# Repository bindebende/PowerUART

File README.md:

# PowerUART
Under Development!!!
USB to UART converter with Type C connector and 100W Power Delivery

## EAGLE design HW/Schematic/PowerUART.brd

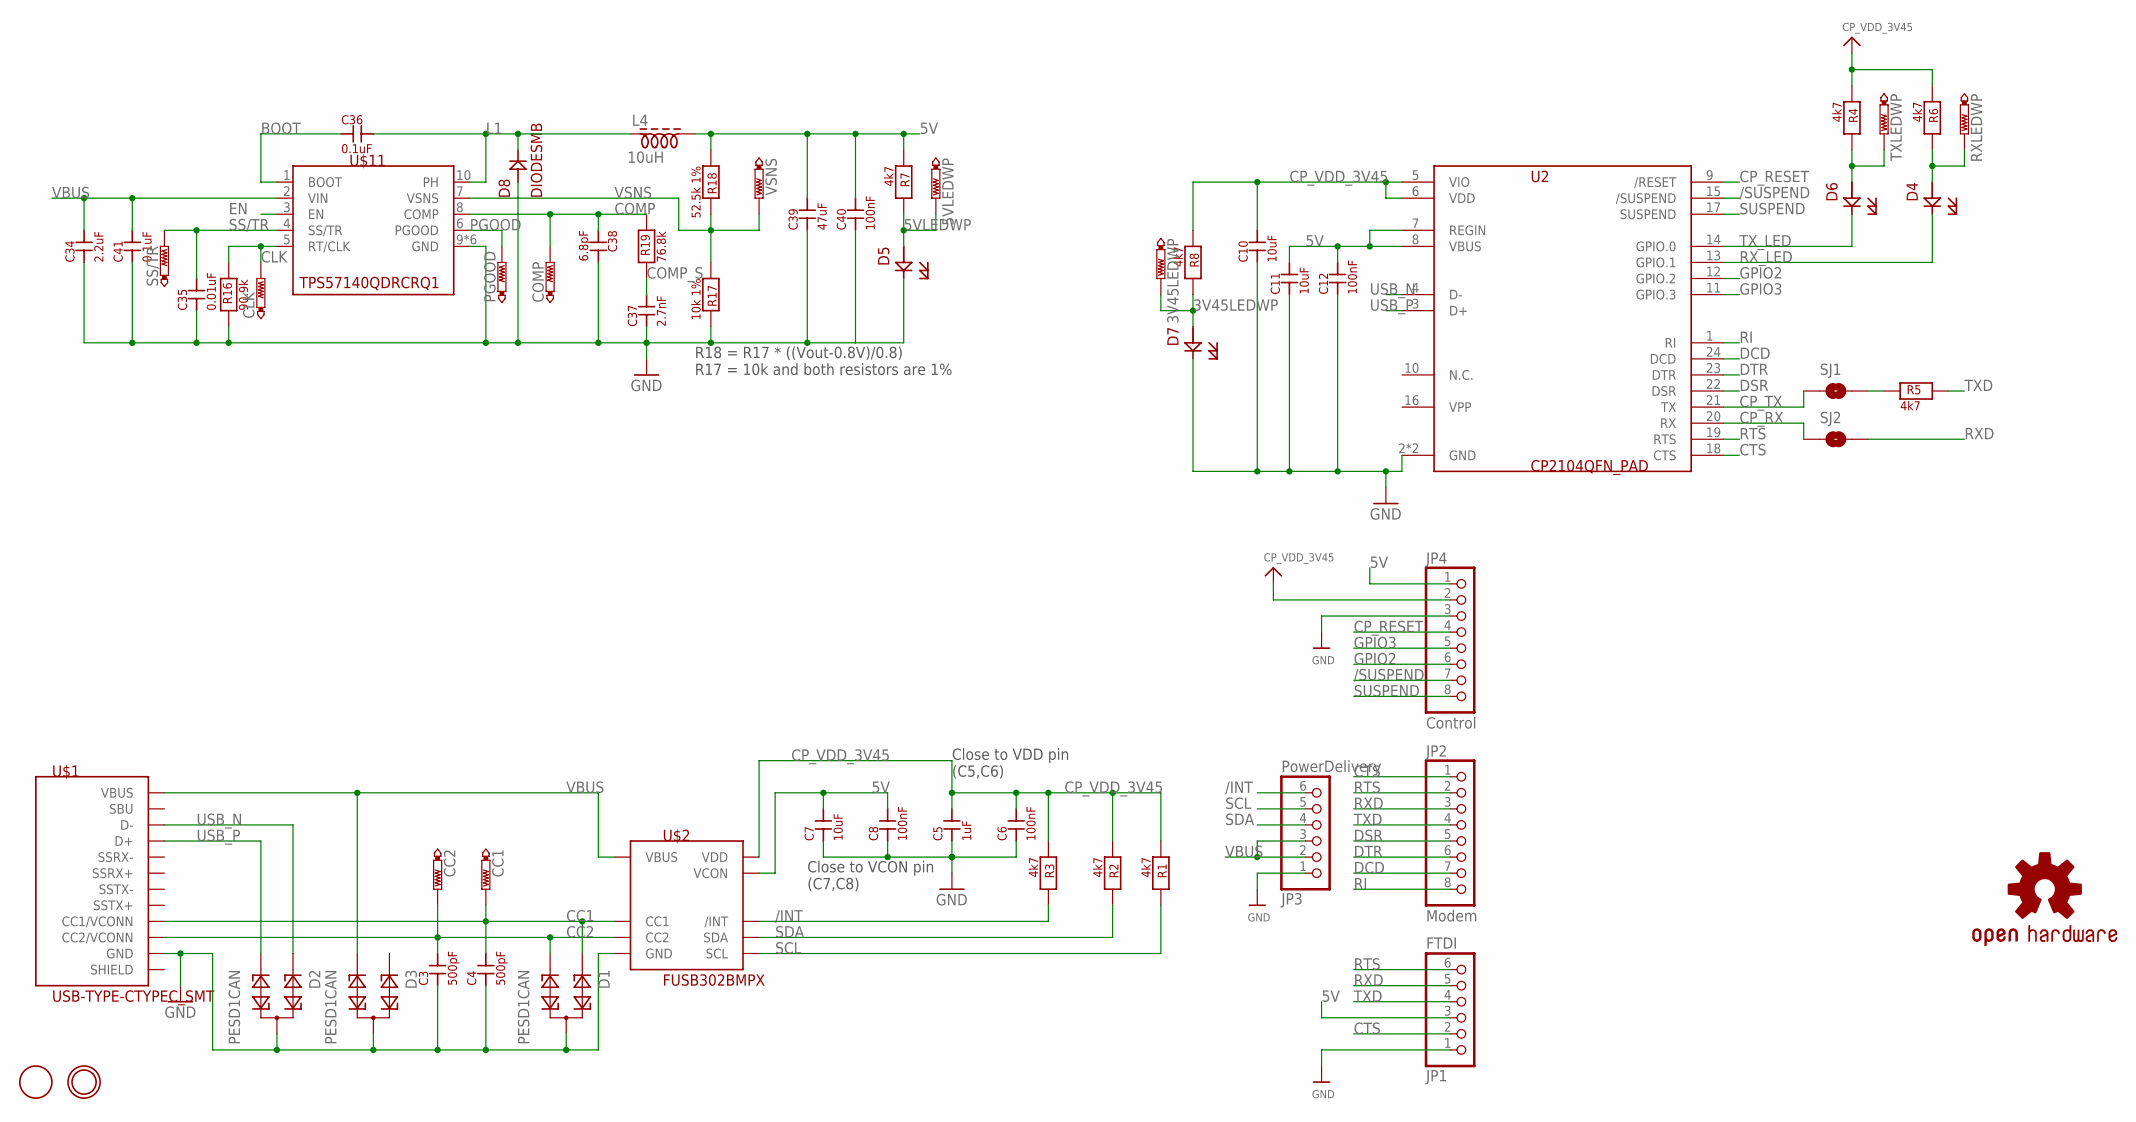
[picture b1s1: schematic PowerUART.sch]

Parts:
3V45LEDWP, 5VLEDWP: CP_RESET; B1,27
C3, C4: 500pF; C0402K
C5: 1uF; C0402K
C6, C8, C12, C40: 100nF; C0402K
C7, C10, C11: 10uF; C0402K
C34: 2.2uF; SM-1206
C35: 0.01uF; C0402K
C36, C41: 0.1uF; C0402K
C37: 2.7nF; C0402K
C38: 6.8pF; C0402K
C39: 47uF; SM-1206
CC1, CC2: CP_RESET; B1,27
CLK: CP_RESET; B1,27
COMP: CP_RESET; B1,27
D1, D2, D3: PESD1CAN; SOT23
D4, D5, D6, D7: LED; CHIP-LED0805
D8: DIODESMB; SMBJ
GND: MOUNTINGHOLE2.0; MOUNTINGHOLE_2.0_PLATED
JP1: FTDI; 1X06_ROUND_76
JP2: Modem; 1X08_ROUND_70
JP3: PowerDelivery; 1X06_ROUND_76
JP4: Control; 1X08_ROUND_70
L4: 10uH; DFN600X600X420-2
LOGO1: OSHW-LOGOMINI; OSHW-LOGO-MINI
PGOOD: CP_RESET; B1,27
R1, R2, R3, R4, R5, R6, R7, R8: 4k7; R0402
R16: 90.9k; R0402
R17: 10k 1%; R0402
R18: 52.5k 1%; R0402
R19: 76.8k; R0402
RXLEDWP: CP_RESET; B1,27
SJ1, SJ2: SOLDERJUMPER-OLDTRACE; SJ_2S-TRACE
SS/TR: CP_RESET; B1,27
TP2: FIDUCIAL; FIDUCIAL_1MM
TXLEDWP: CP_RESET; B1,27
U2: CP2104QFN_PAD; QFN50P400X400X80-25T245
U$1: USB-TYPE-CTYPEC_SMT; TYPECSMT
U$2: FUSB302BMPX; QFN50P250X250X80-15T150
U$11: TPS57140QDRCRQ1; VSON10
VSNS: CP_RESET; B1,27

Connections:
3V45LEDWP: 3V45LEDWP.TP, D7.A (_), R8.2 (__)
5V: C7.2 (__), C8.2 (__), C11.2 (__), C12.2 (__), C39.2 (__), C40.2 (__), JP1.3, JP4.1, L4.2, R7.1 (_), R18.1 (_), U2.7 (REGIN), U2.8 (VBUS), U$2.12 (VCON), U$2.13 (VCON)
5VLEDWP: 5VLEDWP.TP, D5.A (_), R7.2 (__)
/INT: JP3.6, R3.2 (__), U$2.5 (/INT)
/SUSPEND: JP4.7, U2.15 (/SUSPEND)
BOOT: C36.1 (_), U$11.1 (BOOT)
CC1: C4.2 (__), CC1.TP, D1.1, U$1.A5 (CC1/VCONN), U$2.10 (CC1), U$2.11 (CC1)
CC2: C3.2 (__), CC2.TP, D1.2, U$1.B5 (CC2/VCONN), U$2.1 (CC2), U$2.14 (CC2)
CLK: CLK.TP, R16.2 (__), U$11.5 (RT/CLK)
COMP: C38.1 (_), COMP.TP, R19.2 (__), U$11.8 (COMP)
COMP_S: C37.2 (__), R19.1 (_)
CP_RESET: JP4.4, U2.9 (/RESET)
CP_RX: SJ2.1, U2.20 (RX)
CP_TX: SJ1.1, U2.21 (TX)
CP_VDD_3V45: C5.2 (__), C6.2 (__), C10.2 (__), JP4.2, R1.1 (_), R2.1 (_), R3.1 (_), R4.1 (_), R6.1 (_), R8.1 (_), U2.5 (VIO), U2.6 (VDD), U$2.3 (VDD), U$2.4 (VDD)
CTS: JP1.2, JP2.1, U2.18 (CTS)
DCD: JP2.7, U2.24 (DCD)
DSR: JP2.5, U2.22 (DSR)
DTR: JP2.6, U2.23 (DTR)
EN: U$11.3 (EN)
GND: C3.1 (_), C4.1 (_), C5.1 (_), C6.1 (_), C7.1 (_), C8.1 (_), C10.1 (_), C11.1 (_), C12.1 (_), C34.1 (_), C35.1 (_), C37.1 (_), C38.2 (__), C39.1 (_), C40.1 (_), C41.1 (_), D1.3, D2.3, D3.3, D5.C (__), D7.C (__), D8.A, JP1.1, JP3.1, JP4.3, R16.1 (_), R17.2 (__), U2.2 (GND), U2.25 (GND), U$1.A1 (GND), U$1.A12 (GND), U$1.B1 (GND), U$1.B12 (GND), U$2.8 (GND), U$2.9 (GND), U$2.15 (GND), U$11.9 (GND), U$11.11 (GND), U$11.12 (GND), U$11.13 (GND), U$11.14 (GND), U$11.15 (GND)
GPIO2: JP4.6, U2.12 (GPIO.2)
GPIO3: JP4.5, U2.11 (GPIO.3)
L1: C36.2 (__), D8.C, L4.1, U$11.10 (PH)
unnamed: R5.1 (_), SJ1.2
PGOOD: PGOOD.TP, U$11.6 (PGOOD)
RI: JP2.8, U2.1 (RI)
RTS: JP1.6, JP2.2, U2.19 (RTS)
RXD: JP1.5, JP2.3, SJ2.2
RXLEDWP: D4.A (_), R6.2 (__), RXLEDWP.TP
RX_LED: D4.C (__), U2.13 (GPIO.1)
SCL: JP3.5, R1.2 (__), U$2.6 (SCL)
SDA: JP3.4, R2.2 (__), U$2.7 (SDA)
SS/TR: C35.2 (__), SS/TR.TP, U$11.4 (SS/TR)
SUSPEND: JP4.8, U2.17 (SUSPEND)
TXD: JP1.4, JP2.4, R5.2 (__)
TXLEDWP: D6.A (_), R4.2 (__), TXLEDWP.TP
TX_LED: D6.C (__), U2.14 (GPIO.0)
USB_N: D2.1, U2.4 (D-), U$1.A7 (D-), U$1.B7 (D-)
USB_P: D2.2, U2.3 (D+), U$1.A6 (D+), U$1.B6 (D+)
VBUS: C34.2 (__), C41.2 (__), D3.2, JP3.2, JP3.3, U$1.A4 (VBUS), U$1.A9 (VBUS), U$1.B4 (VBUS), U$1.B9 (VBUS), U$2.2 (VBUS), U$11.2 (VIN)
VSNS: R17.1 (_), R18.2 (__), U$11.7 (VSNS), VSNS.TP

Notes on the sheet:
Close to VDD pin (C5,C6)
Close to VCON pin (C7,C8)
R18 = R17 * ((Vout-0.8V)/0.8) R17 = 10k and both resistors are 1%

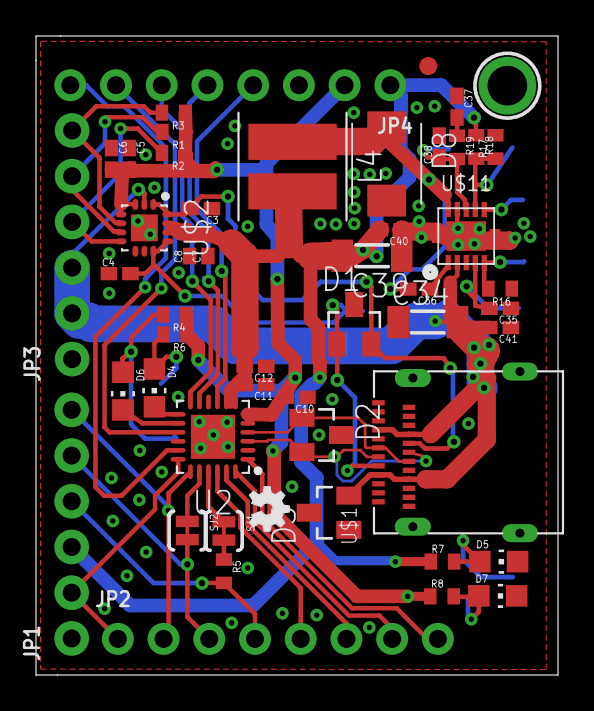
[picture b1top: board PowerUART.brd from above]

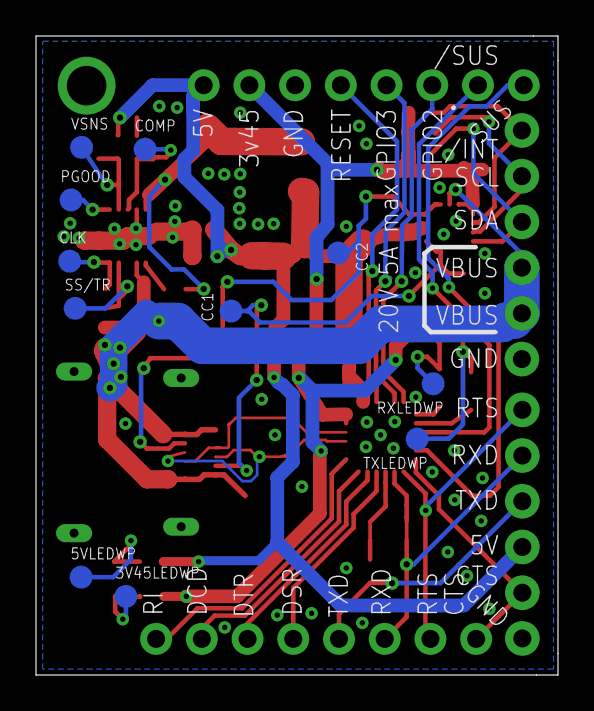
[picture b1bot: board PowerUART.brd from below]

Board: 2 copper layers, 29.0 x 35.5 mm, 62 parts (11 on the bottom side), 41 nets.

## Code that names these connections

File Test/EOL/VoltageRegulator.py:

from silta import stm32f407

class VoltageRegulator:
    __bridge = 0

    # GPIO IN pins
    __PGOOD = 'PD2'
    __CC1 = 'PD0'
    __CC2 = 'PD2'

    # ADC pins
    __COMP = 'PB4'
    __VSNS = 'PA0'
    __LED5VWP = 'PA1'
    __Out5V = 'PA2'
    __SS_TR = 'PB1'
    __CLK = 'PB2'



    def __init__(self, serial):

        self.bridge = stm32f407.bridge(serial)

        # config GPIO inputs
        self.bridge.gpiocfg(self.__PGOOD, 'input')
        self.bridge.gpiocfg(self.__CC1, 'input')
        self.bridge.gpiocfg(self.__CC2, 'input')

        # config Analog inputs
        self.bridge.gpiocfg(self.__COMP, 'analog')
        self.bridge.gpiocfg(self.__VSNS, 'analog')
        self.bridge.gpiocfg(self.__LED5VWP, 'analog')
        self.bridge.gpiocfg(self.__Out5V, 'analog')
        self.bridge.gpiocfg(self.__CLK, 'analog')
        self.bridge.gpiocfg(self.__SS_TR, 'analog')


    def checkSupply(self):
        result = {}

        value_VSNS = self.bridge.adc(self.__VSNS)

        # compensate the voltage drop from the feedback resistors
        value_VSNS *= 6.25

        if(value_VSNS > 4.9 and value_VSNS < 5.1):
            result['VSNS']={'value':value_VSNS,'result':'Passed'}
        else:
            result['VSNS'] = {'value': value_VSNS, 'result': 'Failed'}

        # read 5v input
        value5V = self.bridge.adc(self.__Out5V)
        # compensate the EOL input voltage divider
        value5V *= 2

        if(value5V > 4.9 and value5V < 5.1):
            result['5v']={'value':value_VSNS,'result':'Passed'}
        else:
            result['5v'] = {'value': value_VSNS, 'result': 'Failed'}

        # read 5v LED input
        value5VLED = self.bridge.adc(self.__Out5V)
        # compensate the EOL input voltage divider
        value5VLED *= 2

        if (value5VLED > 4.9 and value5VLED < 5.1):
            result['5v_LED'] = {'value': value_VSNS, 'result': 'Passed'}
        else:
            result['5v_LED'] = {'value': value_VSNS, 'result': 'Failed'}





        return result

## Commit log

2018-11-14 Base schematic
    Add: - Base schematic
    - Datasheets
2018-11-14 generate schematic pdf
2018-11-17 Add TPS55165
    Add TPS55165 and it’s circuitry
    layout file is created
2018-11-17 Add high level design regenerate schematic pdf
2018-11-17 Add HLD picture to readme
2018-11-20 Finish pre layout
    Generate layout pdfs
2018-11-23 Add BOM
2018-11-24 change project name
2018-11-24 rename files according to the new project name
2018-11-24 Update BOM
2018-11-24 Add labels
2018-11-25 add testpoints.csv
2018-11-25 csv formatting testpoint.csv
2018-11-25 Add silta based EOL Tests

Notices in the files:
parts and their libraries:
microbuilder: This work is placed in the public domain, and may be freely used for commercial and non-commercial work with the following conditions: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
SparkFun-Retired: Licensing:Creative Commons ShareAlike 4.0 International - https://creativecommons.org/licenses/by-sa/4.0
